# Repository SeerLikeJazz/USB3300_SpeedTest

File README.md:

# USB3300_SpeedTest
stm32407+Usb3300, HS USB2.0 speed test  

## Todo
- 用python测试USB发送接收速度

### 23.11.28
- USB接口不给stm32芯片供电，需要从VIN5V供电
- 整理之前的资料

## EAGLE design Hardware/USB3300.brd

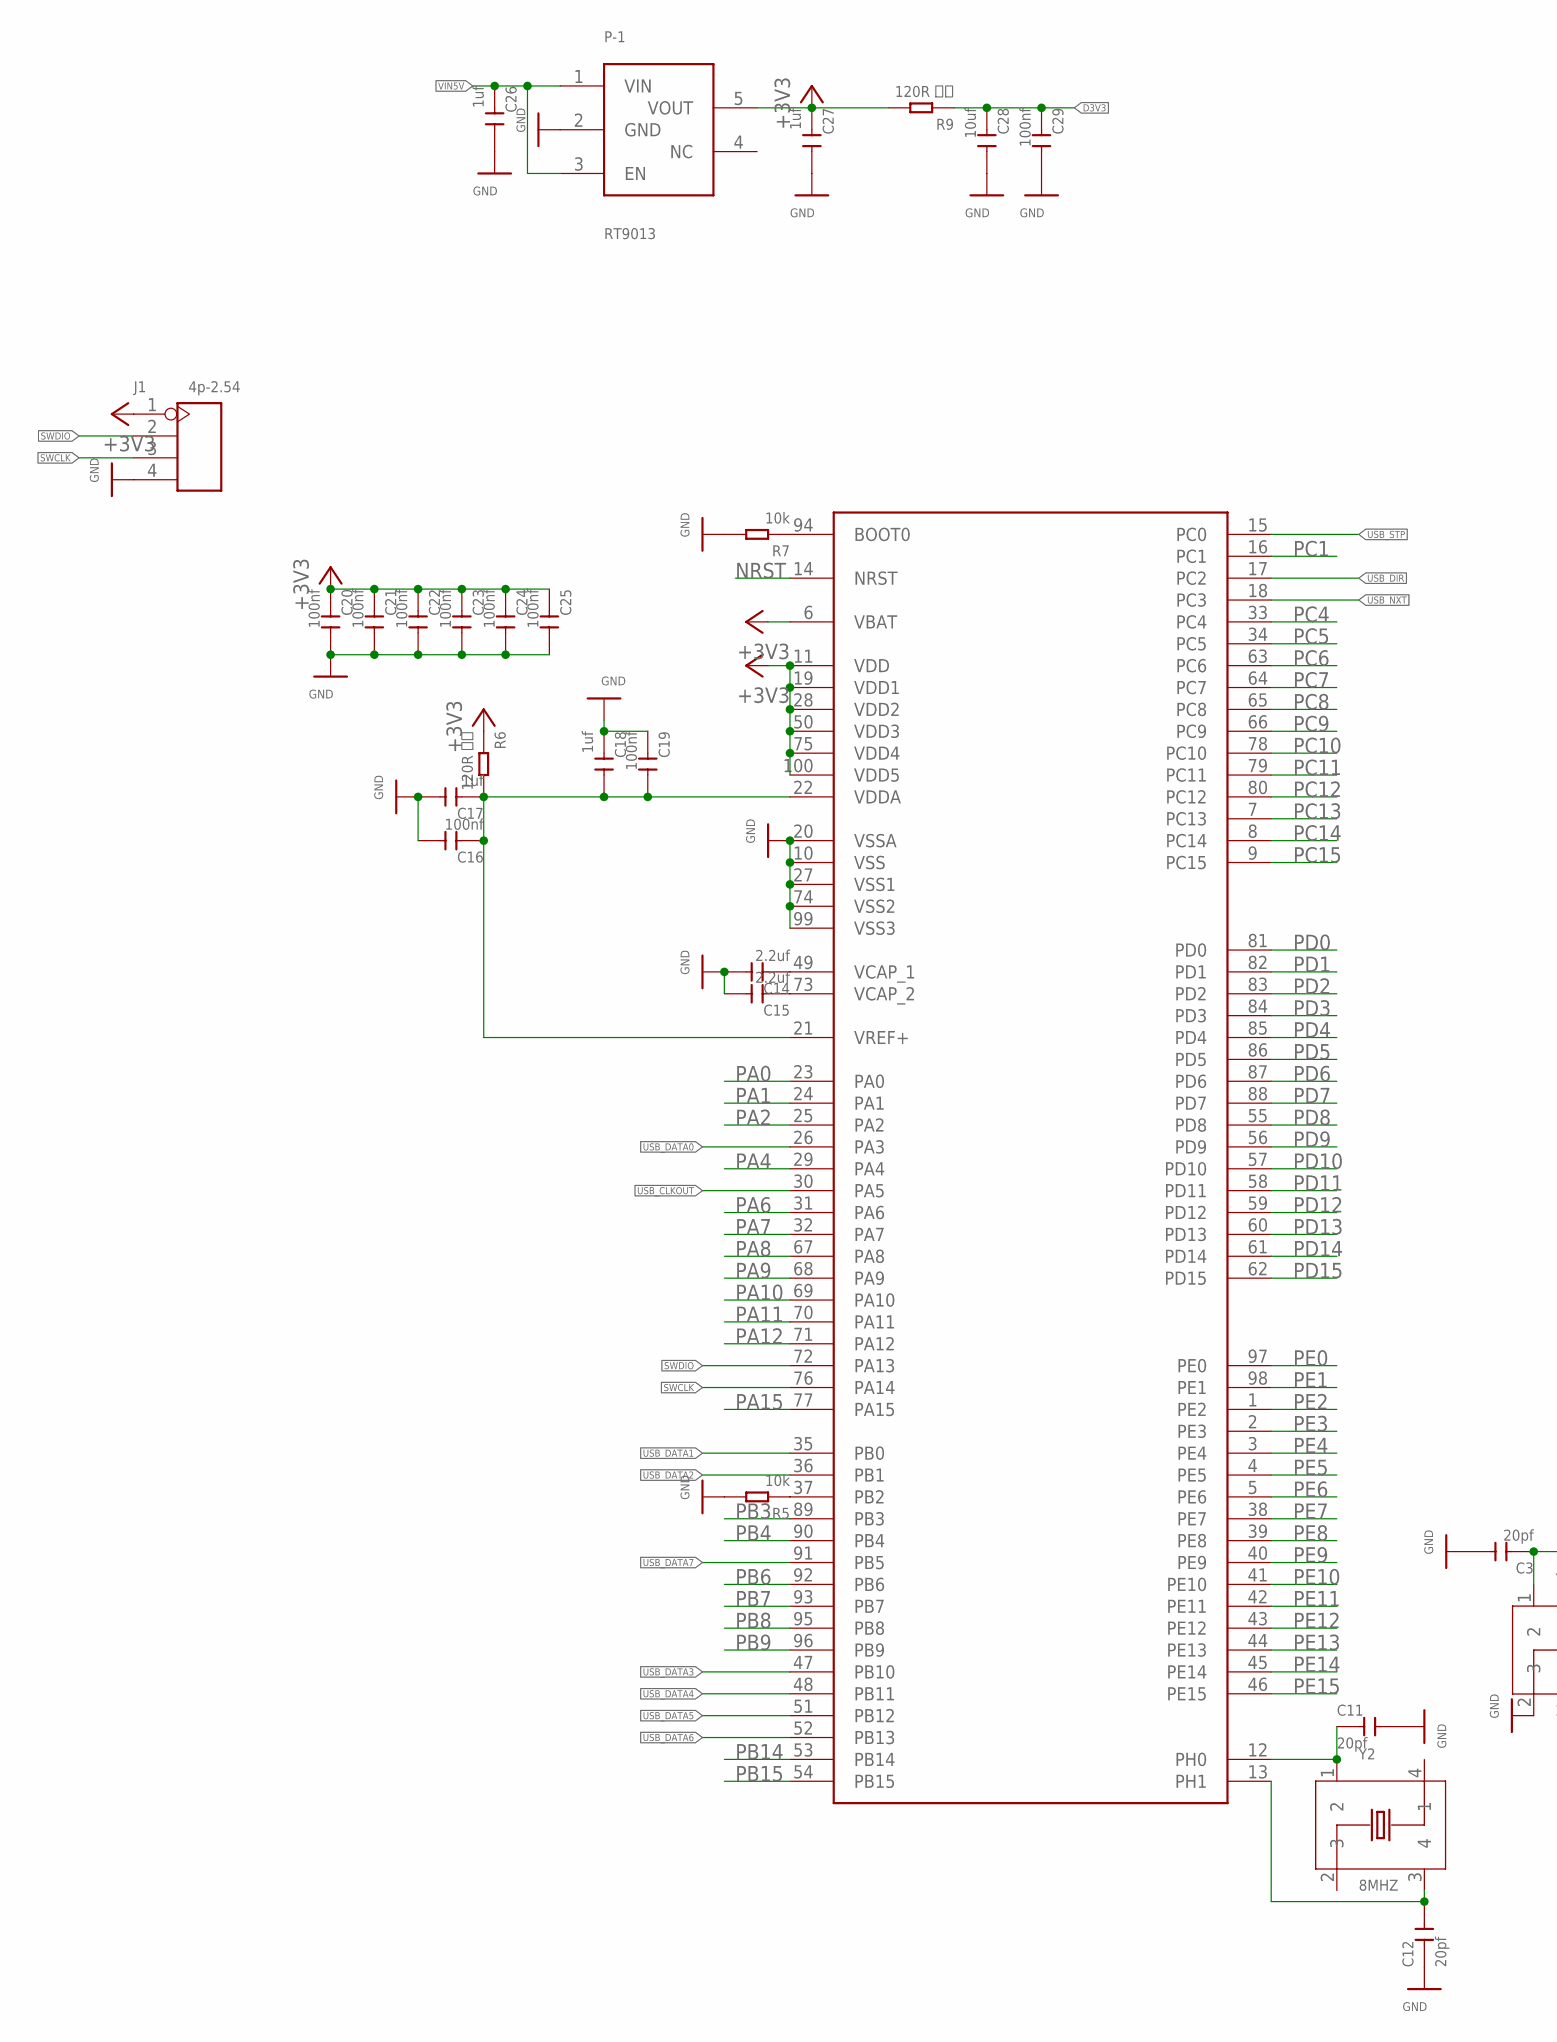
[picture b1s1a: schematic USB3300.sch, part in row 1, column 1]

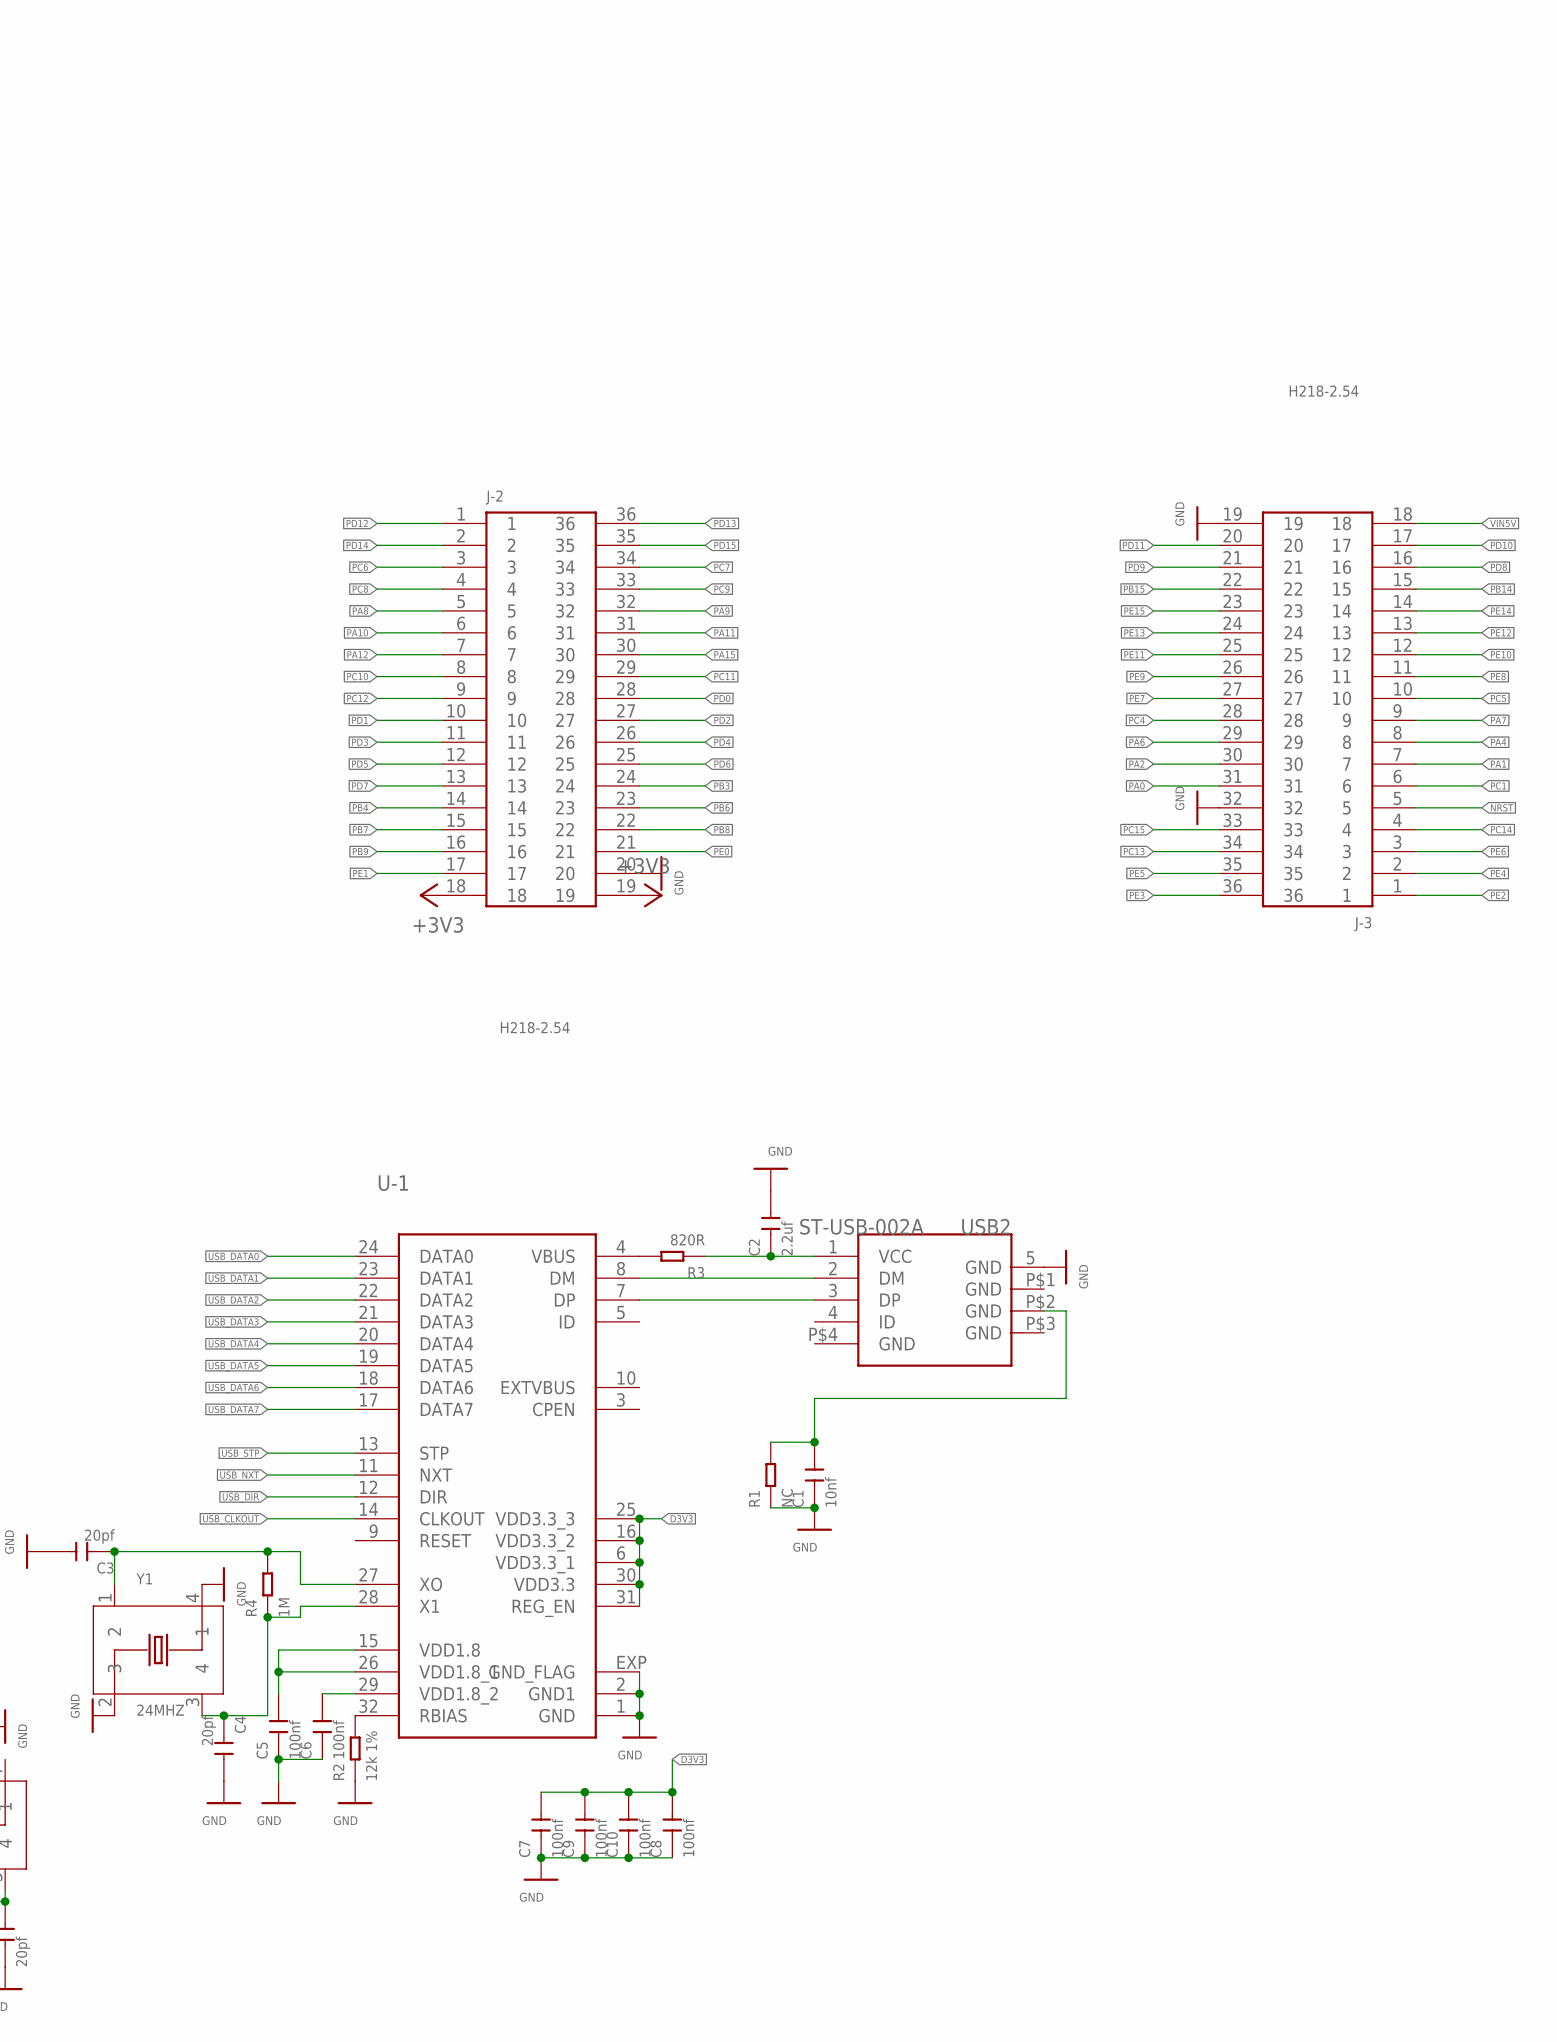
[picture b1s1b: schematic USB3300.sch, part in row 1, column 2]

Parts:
C1: 10nf; C0603
C2, C14, C15: 2.2uf; C0603
C3, C4, C11, C12: 20pf; C0603
C5, C6, C7, C8, C9, C10, C16, C19, C20, C21, C22, C23, C24, C25, C29: 100nf; C0603
C17, C18, C26, C27: 1uf; C0603
C28: 10uf; C0603
J1: 4p-2.54; H4-2.54
J-2, J-3: H218-2.54; H2X18-2.54
P-1: RT9013; SOT23-5
R1: NC; R0603
R2: 12k 1%; R0603
R3: 820R; R0603
R4: 1M; R0603
R5, R7: 10k; R0603
R6, R9: 120R 磁珠; R0603
U$1: STM32F40XSTM32D40X; LQFP100
U-1: USB3300; QFN32
USB2: ST-USB-002A; MINIUSB5+4P-SMD-0.8-90D
Y1: 24MHZ; X4-SMD-3.2X2.5X0.7MM
Y2: 8MHZ; X4-SMD-3.2X2.5X0.7MM

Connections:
+3V3: C20.1, C21.1, C22.1, C23.1, C24.1, C25.1, C27.1, J1.1, J-2.18, J-2.19, P-1.5 (VOUT), R6.1, R9.2, U$1.6 (VBAT), U$1.11 (VDD), U$1.19 (VDD1), U$1.28 (VDD2), U$1.50 (VDD3), U$1.75 (VDD4), U$1.100 (VDD5)
D3V3: C7.2, C8.2, C9.2, C10.2, C28.1, C29.1, R9.1, U-1.6 (VDD3.3_1), U-1.16 (VDD3.3_2), U-1.25 (VDD3.3_3), U-1.30 (VDD3.3), U-1.31 (REG_EN)
GND: C1.1, C2.2, C3.2, C4.2, C5.1, C6.1, C7.1, C8.1, C9.1, C10.1, C11.2, C12.1, C14.2, C15.2, C16.2, C17.2, C18.1, C19.1, C20.2, C21.2, C22.2, C23.2, C24.2, C25.2, C26.2, C27.2, C28.2, C29.2, J1.4, J-2.20, J-3.19, J-3.32, P-1.2 (GND), R1.1, R2.1, R5.2, R7.2, U$1.10 (VSS), U$1.20 (VSSA), U$1.27 (VSS1), U$1.74 (VSS2), U$1.99 (VSS3), U-1.1 (GND), U-1.2 (GND1), U-1.EXP (GND_FLAG), USB2.5 (GND), Y1.2 (3), Y1.4 (1)
unnamed: U-1.8 (DM), USB2.2 (DM)
unnamed: U-1.7 (DP), USB2.3 (DP)
unnamed: C3.1, R4.2, U-1.27 (XO), Y1.1 (2)
unnamed: R2.2, U-1.32 (RBIAS)
unnamed: R3.2, U-1.4 (VBUS)
unnamed: C4.1, R4.1, U-1.28 (X1), Y1.3 (4)
unnamed: C5.2, U-1.15 (VDD1.8), U-1.26 (VDD1.8_1)
unnamed: C6.2, U-1.29 (VDD1.8_2)
unnamed: C11.1, U$1.12 (PH0), Y2.1 (2)
unnamed: C12.2, U$1.13 (PH1), Y2.3 (4)
unnamed: R7.1, U$1.94 (BOOT0)
unnamed: C16.1, C17.1, C18.2, C19.2, R6.2, U$1.21 (VREF+), U$1.22 (VDDA)
unnamed: C14.1, U$1.49 (VCAP_1)
unnamed: C15.1, U$1.73 (VCAP_2)
unnamed: C2.1, R3.1, USB2.1 (VCC)
unnamed: R5.1, U$1.37 (PB2)
unnamed: C1.2, R1.2, USB2.P$2 (GND)
NRST: J-3.5, U$1.14 (NRST)
PA0: J-3.31, U$1.23 (PA0)
PA1: J-3.7, U$1.24 (PA1)
PA2: J-3.30, U$1.25 (PA2)
PA4: J-3.8, U$1.29 (PA4)
PA6: J-3.29, U$1.31 (PA6)
PA7: J-3.9, U$1.32 (PA7)
PA8: J-2.5, U$1.67 (PA8)
PA9: J-2.32, U$1.68 (PA9)
PA10: J-2.6, U$1.69 (PA10)
PA11: J-2.31, U$1.70 (PA11)
PA12: J-2.7, U$1.71 (PA12)
PA15: J-2.30, U$1.77 (PA15)
PB3: J-2.24, U$1.89 (PB3)
PB4: J-2.14, U$1.90 (PB4)
PB6: J-2.23, U$1.92 (PB6)
PB7: J-2.15, U$1.93 (PB7)
PB8: J-2.22, U$1.95 (PB8)
PB9: J-2.16, U$1.96 (PB9)
PB14: J-3.15, U$1.53 (PB14)
PB15: J-3.22, U$1.54 (PB15)
PC1: J-3.6, U$1.16 (PC1)
PC4: J-3.28, U$1.33 (PC4)
PC5: J-3.10, U$1.34 (PC5)
PC6: J-2.3, U$1.63 (PC6)
PC7: J-2.34, U$1.64 (PC7)
PC8: J-2.4, U$1.65 (PC8)
PC9: J-2.33, U$1.66 (PC9)
PC10: J-2.8, U$1.78 (PC10)
PC11: J-2.29, U$1.79 (PC11)
PC12: J-2.9, U$1.80 (PC12)
PC13: J-3.34, U$1.7 (PC13)
PC14: J-3.4, U$1.8 (PC14)
PC15: J-3.33, U$1.9 (PC15)
PD0: J-2.28, U$1.81 (PD0)
PD1: J-2.10, U$1.82 (PD1)
PD2: J-2.27, U$1.83 (PD2)
PD3: J-2.11, U$1.84 (PD3)
PD4: J-2.26, U$1.85 (PD4)
PD5: J-2.12, U$1.86 (PD5)
PD6: J-2.25, U$1.87 (PD6)
PD7: J-2.13, U$1.88 (PD7)
PD8: J-3.16, U$1.55 (PD8)
PD9: J-3.21, U$1.56 (PD9)
PD10: J-3.17, U$1.57 (PD10)
PD11: J-3.20, U$1.58 (PD11)
PD12: J-2.1, U$1.59 (PD12)
PD13: J-2.36, U$1.60 (PD13)
PD14: J-2.2, U$1.61 (PD14)
PD15: J-2.35, U$1.62 (PD15)
PE0: J-2.21, U$1.97 (PE0)
PE1: J-2.17, U$1.98 (PE1)
PE2: J-3.1, U$1.1 (PE2)
PE3: J-3.36, U$1.2 (PE3)
PE4: J-3.2, U$1.3 (PE4)
PE5: J-3.35, U$1.4 (PE5)
PE6: J-3.3, U$1.5 (PE6)
PE7: J-3.27, U$1.38 (PE7)
PE8: J-3.11, U$1.39 (PE8)
PE9: J-3.26, U$1.40 (PE9)
PE10: J-3.12, U$1.41 (PE10)
PE11: J-3.25, U$1.42 (PE11)
PE12: J-3.13, U$1.43 (PE12)
PE13: J-3.24, U$1.44 (PE13)
PE14: J-3.14, U$1.45 (PE14)
PE15: J-3.23, U$1.46 (PE15)
SWCLK: J1.3, U$1.76 (PA14)
SWDIO: J1.2, U$1.72 (PA13)
USB_CLKOUT: U$1.30 (PA5), U-1.14 (CLKOUT)
USB_DATA0: U$1.26 (PA3), U-1.24 (DATA0)
USB_DATA1: U$1.35 (PB0), U-1.23 (DATA1)
USB_DATA2: U$1.36 (PB1), U-1.22 (DATA2)
USB_DATA3: U$1.47 (PB10), U-1.21 (DATA3)
USB_DATA4: U$1.48 (PB11), U-1.20 (DATA4)
USB_DATA5: U$1.51 (PB12), U-1.19 (DATA5)
USB_DATA6: U$1.52 (PB13), U-1.18 (DATA6)
USB_DATA7: U$1.91 (PB5), U-1.17 (DATA7)
USB_DIR: U$1.17 (PC2), U-1.12 (DIR)
USB_NXT: U$1.18 (PC3), U-1.11 (NXT)
USB_STP: U$1.15 (PC0), U-1.13 (STP)
VIN5V: C26.1, J-3.18, P-1.1 (VIN), P-1.3 (EN)

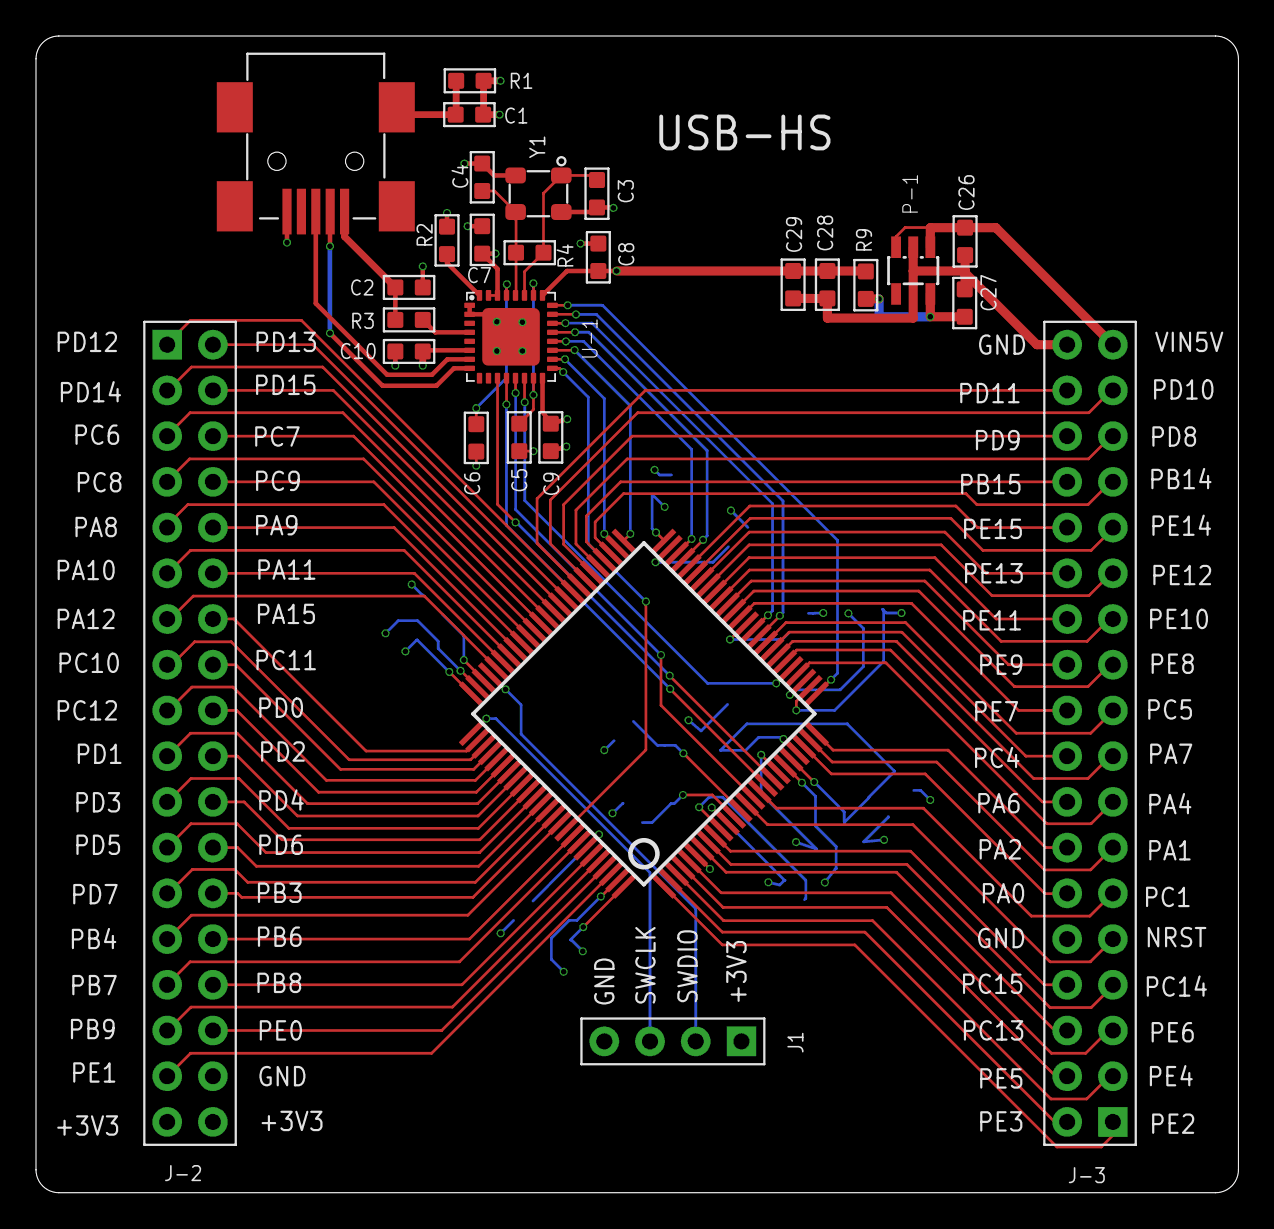
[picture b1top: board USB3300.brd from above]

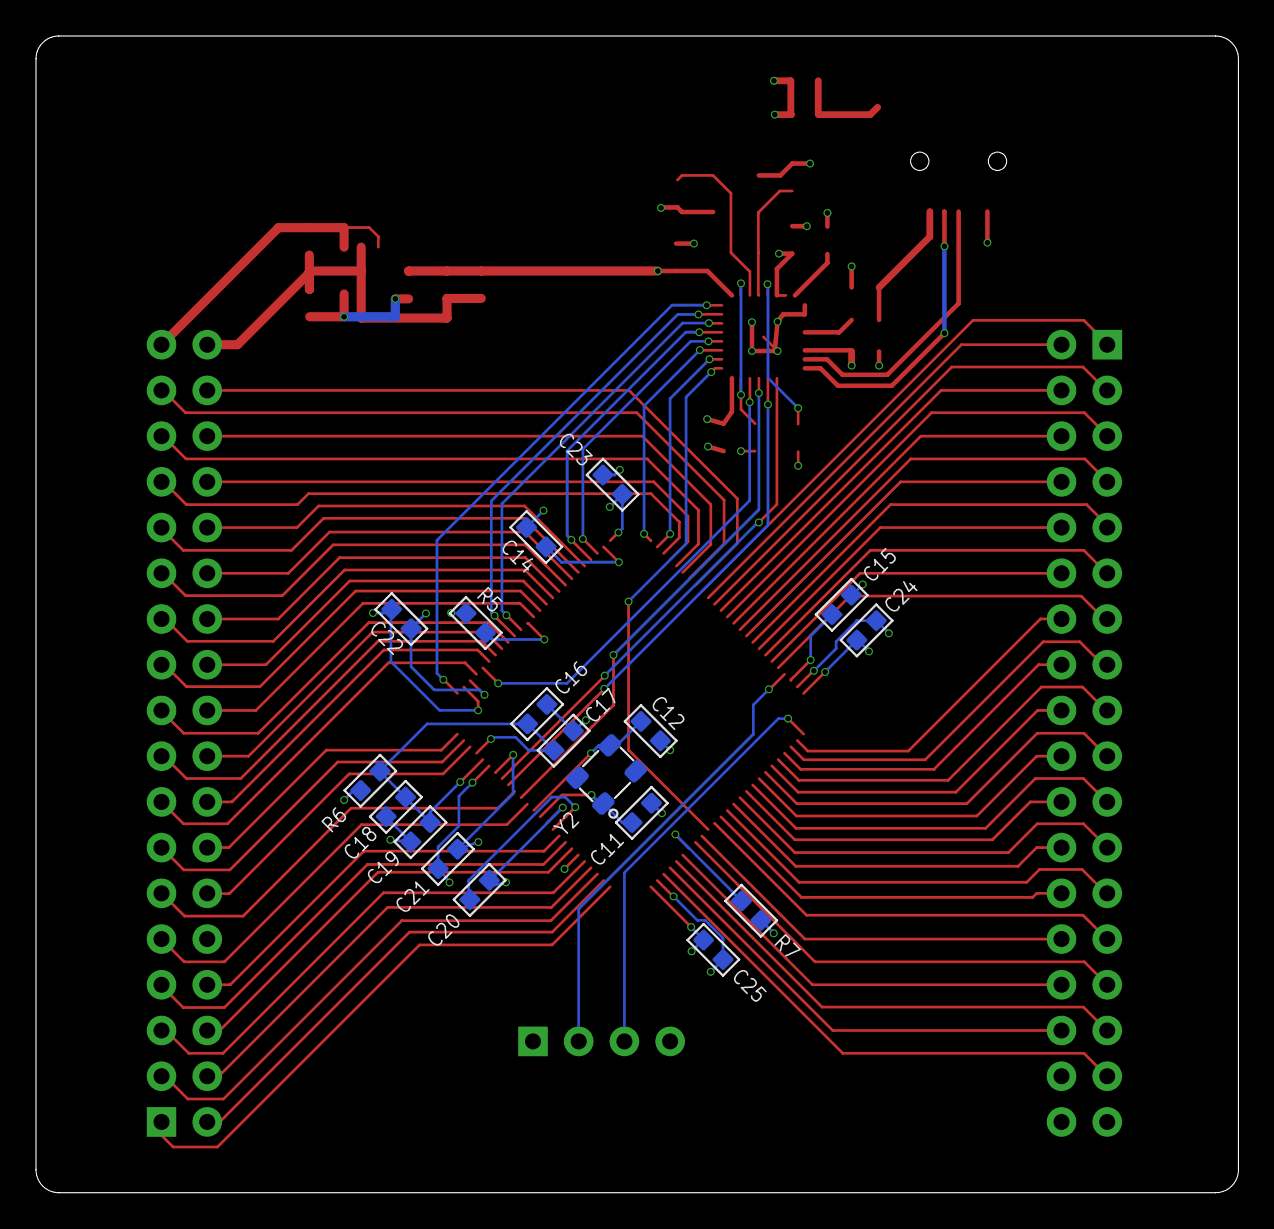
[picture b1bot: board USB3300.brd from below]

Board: 4 copper layers, 66.8 x 64.3 mm, 45 parts (18 on the bottom side), 101 nets.

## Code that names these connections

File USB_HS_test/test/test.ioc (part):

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Mcu.Name=STM32F407I(E-G)Tx
Mcu.Package=LQFP176
Mcu.UserName=STM32F407IGTx
PA13.Mode=Serial_Wire
PA13.Signal=SYS_JTMS-SWDIO
PA14.Mode=Serial_Wire
PA14.Signal=SYS_JTCK-SWCLK
PA3.Mode=Device_HS
PA3.Signal=USB_OTG_HS_ULPI_D0
PA5.Mode=Device_HS
PA5.Signal=USB_OTG_HS_ULPI_CK
PB0.Mode=Device_HS
PB0.Signal=USB_OTG_HS_ULPI_D1
PB1.Mode=Device_HS
PB1.Signal=USB_OTG_HS_ULPI_D2
PB10.Mode=Device_HS
PB10.Signal=USB_OTG_HS_ULPI_D3
PB11.Mode=Device_HS
PB11.Signal=USB_OTG_HS_ULPI_D4
PB12.Mode=Device_HS
PB12.Signal=USB_OTG_HS_ULPI_D5
PB13.Mode=Device_HS
PB13.Signal=USB_OTG_HS_ULPI_D6
PB5.Mode=Device_HS
PB5.Signal=USB_OTG_HS_ULPI_D7
PC0.Mode=Device_HS
PC0.Signal=USB_OTG_HS_ULPI_STP
PH0-OSC_IN.Mode=HSE-External-Oscillator
PH0-OSC_IN.Signal=RCC_OSC_IN
PH1-OSC_OUT.Mode=HSE-External-Oscillator
PH1-OSC_OUT.Signal=RCC_OSC_OUT
PH4.Mode=Device_HS
PH4.Signal=USB_OTG_HS_ULPI_NXT
PI11.Mode=Device_HS
PI11.Signal=USB_OTG_HS_ULPI_DIR
RCC.HSE_VALUE=8000000
RCC.SYSCLKFreq_VALUE=168000000
RCC.SYSCLKSource=RCC_SYSCLKSOURCE_PLLCLK
board=custom

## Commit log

2023-11-28 add previous documents
2023-11-28 add readme
